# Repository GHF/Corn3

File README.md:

Corn3
=====
Copyright (C) 2014 Xo Wang

Corn3 is firmware for Corntroller version 3. It is a total rewrite of previous
Corntroller code, with a focus on writing code and documentation that may serve
as an introduction to three phase motor control for hobbyists.

Build
-----
Corn3 is written for use with GNU Tools for ARM Embedded Processors
(https://launchpad.net/gcc-arm-embedded).

To build, run make:

```
make
```

If you don't have arm-none-eabi in your PATH, specify its prefix in TRGT, e.g.:

```
make TRGT=~/gcc-arm-none-eabi-4_8-2014q3/bin/arm-none-eabi-
```

Hardware
--------
Corntroller is a small and efficient brushless motor controller.

Version 3.2 features:

  - 0.8 in by 1.6 in
  - STM32F3 microcontroller (ARM Cortex-M4 @ 72MHz)
  - TI DRV8301 gate driver, current sense amplifier, and buck converter
  - Three-phase inverter with SO8 N-FETs
  - Dual shunt current sense
  - Hall sensor inputs
  - Up to 30 V input voltage

No power figures available, but should be similar to hobby controllers of
similar size.

Hacking
-------
Corn3 and Corntroller are developed using the Black Magic Probe debugger.

See http://www.blacksphere.co.nz/main/blackmagic

Corntroller v3 has a 10-pin "mini" keyed JTAG header and a PicoBlade 4-pin
serial debug connector. The firmware does not yet support USB firmware
flashing.

License
-------
Corn3 is licensed under the MIT license with non-advertisement clause.

In compliance with the Apache license that ChibiOS configuration and low level
drivers are licensed under, the Apache License version 2.0 is included.

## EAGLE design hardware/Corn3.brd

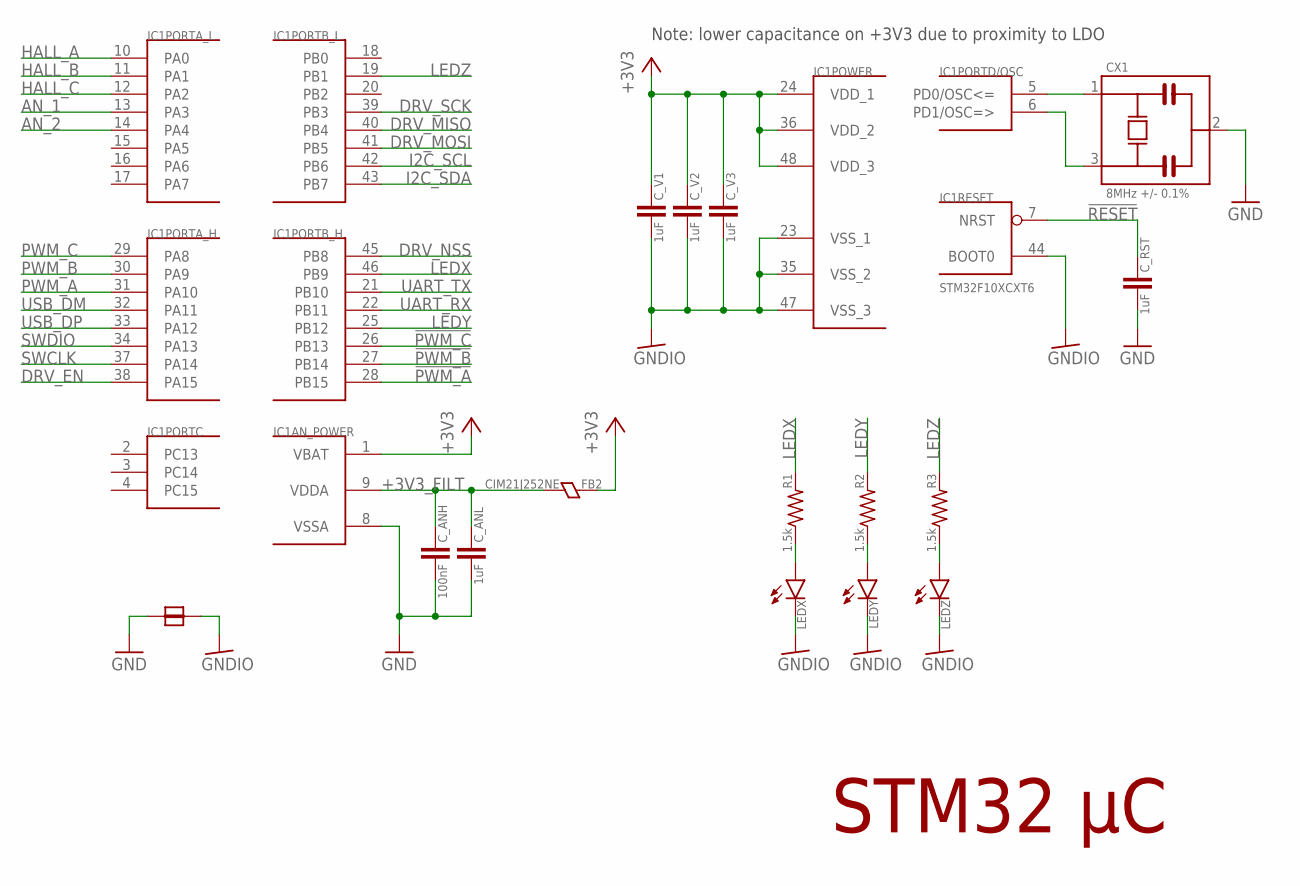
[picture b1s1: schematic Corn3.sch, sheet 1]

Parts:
CX1: 8MHz +/- 0.1%; MURATA_CSTCE
C_ANH: 100nF; 0603
C_ANL: 1uF; 0603
C_RST: 1uF; 0603
C_V1, C_V2, C_V3: 1uF; 0603
FB2: CIM21J252NE; 0805
IC1: STM32F10XCXT6; TQFP48
JUMPER-GND-GNDIO: JUMPER5025; 5025
LEDX: LED0805; 0805_POL
LEDY: LED0805; 0805_POL
LEDZ: LED0805; 0805_POL
R1, R2, R3: 1.5k; 0603

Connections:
!PWM_A: IC1.28 (PB15); also elsewhere on the board
!PWM_B: IC1.27 (PB14); also elsewhere on the board
!PWM_C: IC1.26 (PB13); also elsewhere on the board
!RESET: C_RST.1, IC1.7 (NRST); also elsewhere on the board
+3V3: C_V1.1, C_V2.1, C_V3.1, FB2.2, IC1.1 (VBAT), IC1.24 (VDD_1), IC1.36 (VDD_2), IC1.48 (VDD_3); also elsewhere on the board
+3V3_FILT: C_ANH.1, C_ANL.1, FB2.1, IC1.9 (VDDA); also elsewhere on the board
AN_1: IC1.13 (PA3); also elsewhere on the board
AN_2: IC1.14 (PA4); also elsewhere on the board
DRV_EN: IC1.38 (PA15); also elsewhere on the board
DRV_MISO: IC1.40 (PB4); also elsewhere on the board
DRV_MOSI: IC1.41 (PB5); also elsewhere on the board
DRV_NSS: IC1.45 (PB8); also elsewhere on the board
DRV_SCK: IC1.39 (PB3); also elsewhere on the board
GND: CX1.2, C_ANH.2, C_ANL.2, C_RST.2, IC1.8 (VSSA), JUMPER-GND-GNDIO.1; also elsewhere on the board
GNDIO: C_V1.2, C_V2.2, C_V3.2, IC1.23 (VSS_1), IC1.35 (VSS_2), IC1.44 (BOOT0), IC1.47 (VSS_3), JUMPER-GND-GNDIO.2, LEDX.- (C), LEDY.- (C), LEDZ.- (C)
HALL_A: IC1.10 (PA0); also elsewhere on the board
HALL_B: IC1.11 (PA1); also elsewhere on the board
HALL_C: IC1.12 (PA2); also elsewhere on the board
I2C_SCL: IC1.42 (PB6); also elsewhere on the board
I2C_SDA: IC1.43 (PB7); also elsewhere on the board
LEDX: IC1.46 (PB9), R1.2
LEDY: IC1.25 (PB12), R2.2
LEDZ: IC1.19 (PB1), R3.2
unnamed: CX1.3, IC1.6 (PD1/OSC=>)
unnamed: CX1.1, IC1.5 (PD0/OSC<=)
unnamed: LEDX.+ (A), R1.1
unnamed: LEDZ.+ (A), R3.1
unnamed: LEDY.+ (A), R2.1
PWM_A: IC1.31 (PA10); also elsewhere on the board
PWM_B: IC1.30 (PA9); also elsewhere on the board
PWM_C: IC1.29 (PA8); also elsewhere on the board
SWCLK: IC1.37 (PA14); also elsewhere on the board
SWDIO: IC1.34 (PA13); also elsewhere on the board
UART_RX: IC1.22 (PB11); also elsewhere on the board
UART_TX: IC1.21 (PB10); also elsewhere on the board
USB_DM: IC1.32 (PA11); also elsewhere on the board
USB_DP: IC1.33 (PA12); also elsewhere on the board

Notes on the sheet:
STM32 µC
Note: lower capacitance on +3V3 due to proximity to LDO

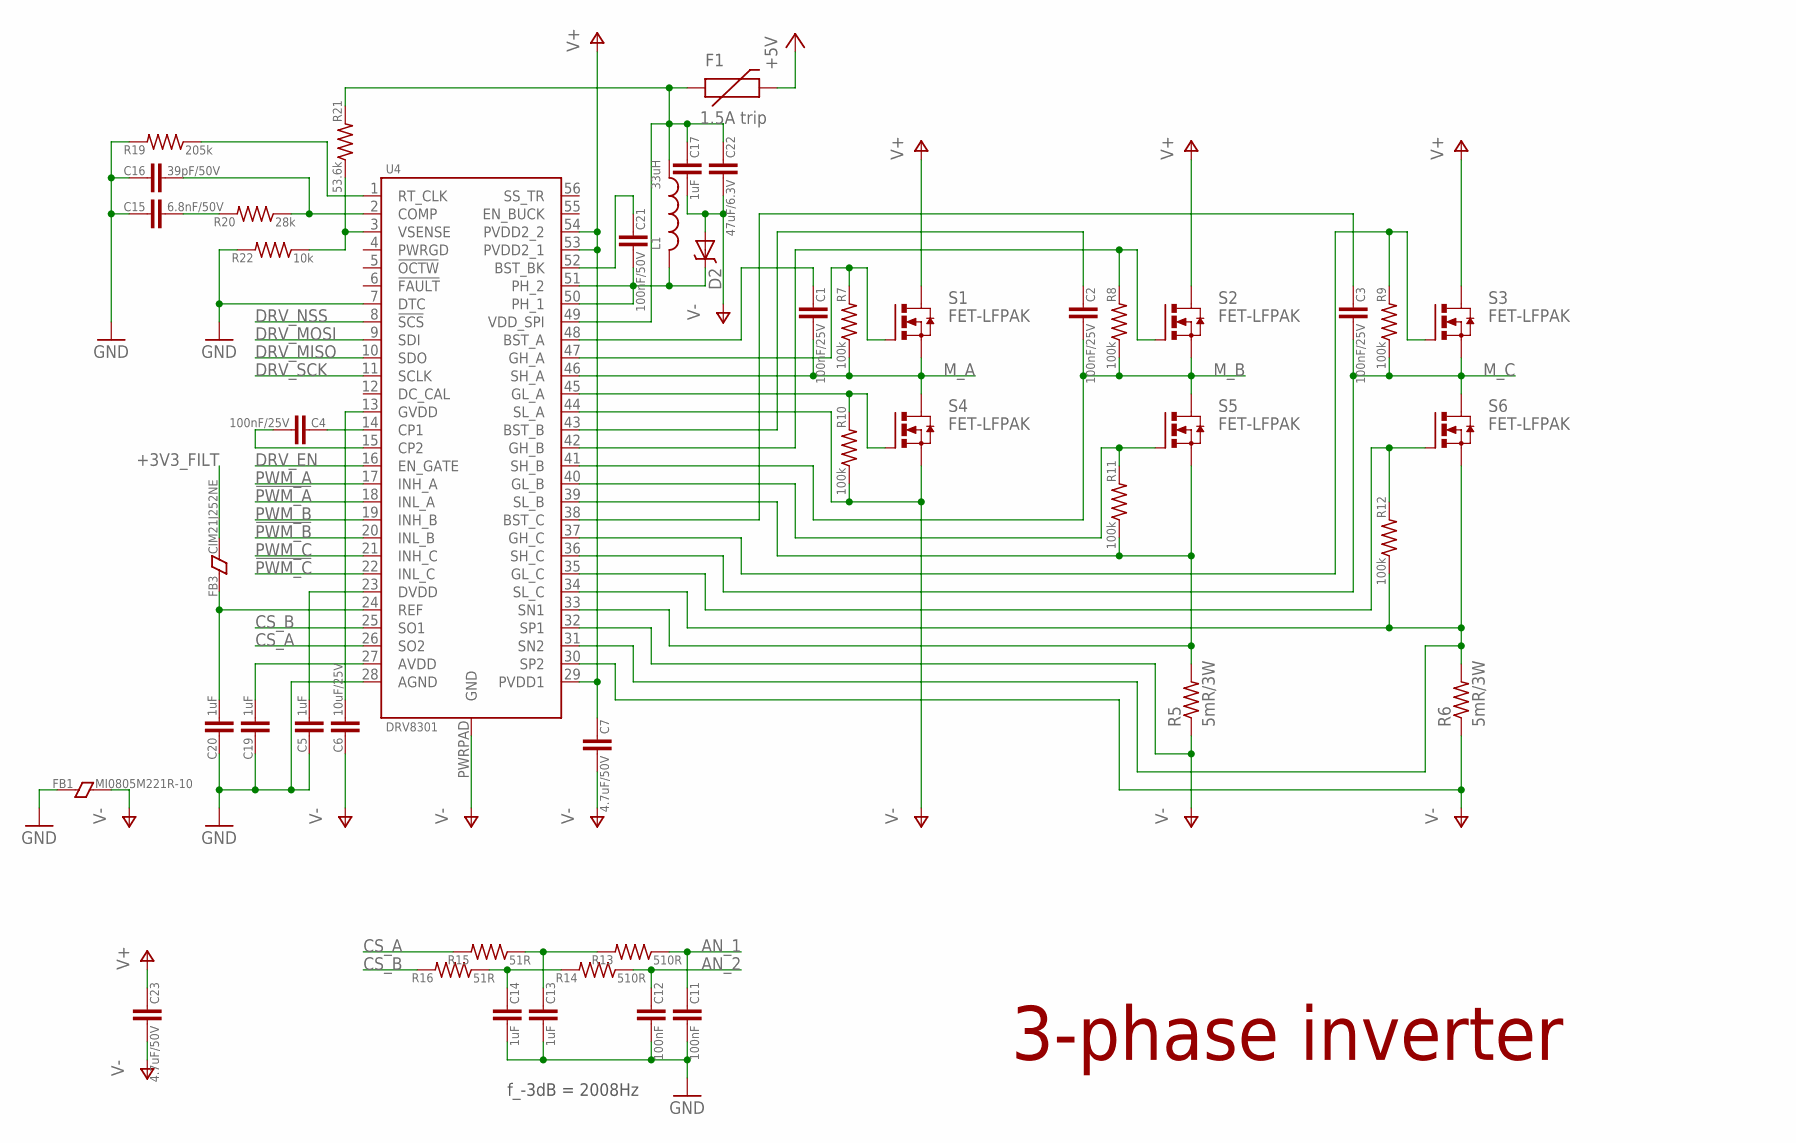
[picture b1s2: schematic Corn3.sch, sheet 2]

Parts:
C1, C2, C3, C4: 100nF/25V; 0603
C5, C13, C14, C17, C19, C20: 1uF; 0603
C6: 10uF/25V; 0805
C7, C23: 4.7uF/50V; 1206
C11, C12: 100nF; 0603
C15: 6.8nF/50V; 0603
C16: 39pF/50V; 0603
C21: 100nF/50V; 0603
C22: 47uF/6.3V; 0805
D2: DIODE-SCHOTTKY_; SMA-DIODE
F1: 1.5A trip; PTC-1206
FB1: MI0805M221R-10; 0805
FB3: CIM21J252NE; 0805
L1: 33uH; TAIYO-YUDEN_NR40
R5, R6: 5mR/3W; R2512
R7, R8, R9, R10, R11, R12: 100k; 0603
R13, R14: 510R; 0603
R15, R16: 51R; 0603
R19: 205k; 0603
R20: 28k; 0603
R21: 53.6k; 0603
R22: 10k; 0603
S1, S2, S3, S4, S5, S6: FET-LFPAK; SON-5X6
U4: DRV8301; HTSSOP-56

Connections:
!PWM_A: U4.18 (INL_A); also elsewhere on the board
!PWM_B: U4.20 (INL_B); also elsewhere on the board
!PWM_C: U4.22 (INL_C); also elsewhere on the board
+3V3_FILT: FB3.1; also elsewhere on the board
+5V: F1.2; also elsewhere on the board
AN_1: C11.1, R13.1; also elsewhere on the board
AN_2: C12.1, R14.1; also elsewhere on the board
CS_A: R15.2, U4.26 (SO2)
CS_B: R16.2, U4.25 (SO1)
DRV_EN: U4.16 (EN_GATE); also elsewhere on the board
DRV_MISO: U4.10 (SDO); also elsewhere on the board
DRV_MOSI: U4.9 (SDI); also elsewhere on the board
DRV_NSS: U4.8 (!SCS); also elsewhere on the board
DRV_SCK: U4.11 (SCLK); also elsewhere on the board
GND: C5.1, C11.2, C12.2, C13.2, C14.2, C15.1, C16.1, C19.1, C20.1, FB1.2, R19.2, R22.2, U4.7 (DTC), U4.28 (AGND); also elsewhere on the board
M_A: C1.2, R7.1, S1.S1 (S), S1.S2 (S), S1.S3 (S), S4.D, S4.D_ (D), U4.46 (SH_A)
M_B: C2.2, R8.1, S2.S1 (S), S2.S2 (S), S2.S3 (S), S5.D, S5.D_ (D), U4.41 (SH_B)
M_C: C3.2, R9.1, S3.S1 (S), S3.S2 (S), S3.S3 (S), S6.D, S6.D_ (D), U4.36 (SH_C)
unnamed: R8.2, S2.G, U4.42 (GH_B)
unnamed: R7.2, S1.G, U4.47 (GH_A)
unnamed: R12.2, S6.G, U4.35 (GL_C)
unnamed: R11.2, S5.G, U4.40 (GL_B)
unnamed: R9.2, S3.G, U4.37 (GH_C)
unnamed: C21.1, U4.52 (BST_BK)
unnamed: C1.1, U4.48 (BST_A)
unnamed: C2.1, U4.43 (BST_B)
unnamed: C3.1, U4.38 (BST_C)
unnamed: R10.2, S4.G, U4.45 (GL_A)
unnamed: C17.1, C22.1, F1.1, L1.1, R21.2, U4.49 (VDD_SPI)
unnamed: C16.2, R20.1, U4.2 (COMP)
unnamed: C14.1, R14.2, R16.1
unnamed: C13.1, R13.2, R15.1
unnamed: C15.2, R20.2
unnamed: R21.1, R22.1, U4.3 (VSENSE)
unnamed: C5.2, U4.23 (DVDD)
unnamed: C6.2, U4.13 (GVDD)
unnamed: C4.1, U4.14 (CP1)
unnamed: C4.2, U4.15 (CP2)
unnamed: C21.2, D2.C, L1.2, U4.50 (PH_1), U4.51 (PH_2)
unnamed: C20.2, FB3.2, U4.24 (REF)
unnamed: C19.2, U4.27 (AVDD)
unnamed: R19.1, U4.1 (RT_CLK)
PWM_A: U4.17 (INH_A); also elsewhere on the board
PWM_B: U4.19 (INH_B); also elsewhere on the board
PWM_C: U4.21 (INH_C); also elsewhere on the board
SL_B: R5.2, R11.1, S5.S1 (S), S5.S2 (S), S5.S3 (S), U4.33 (SN1), U4.39 (SL_B)
SL_C: R6.2, R12.1, S6.S1 (S), S6.S2 (S), S6.S3 (S), U4.31 (SN2), U4.34 (SL_C)
V+: C7.1, C23.1, S1.D, S1.D_ (D), S2.D, S2.D_ (D), S3.D, S3.D_ (D), U4.29 (PVDD1), U4.53 (PVDD2_1), U4.54 (PVDD2_2)
V-: C6.1, C7.2, C17.2, C22.2, C23.2, D2.A, FB1.1, R5.1, R6.1, R10.1, S4.S1 (S), S4.S2 (S), S4.S3 (S), U4.30 (SP2), U4.32 (SP1), U4.44 (SL_A), U4.PWRPAD (GND)

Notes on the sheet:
3-phase inverter
f_-3dB = 2008Hz

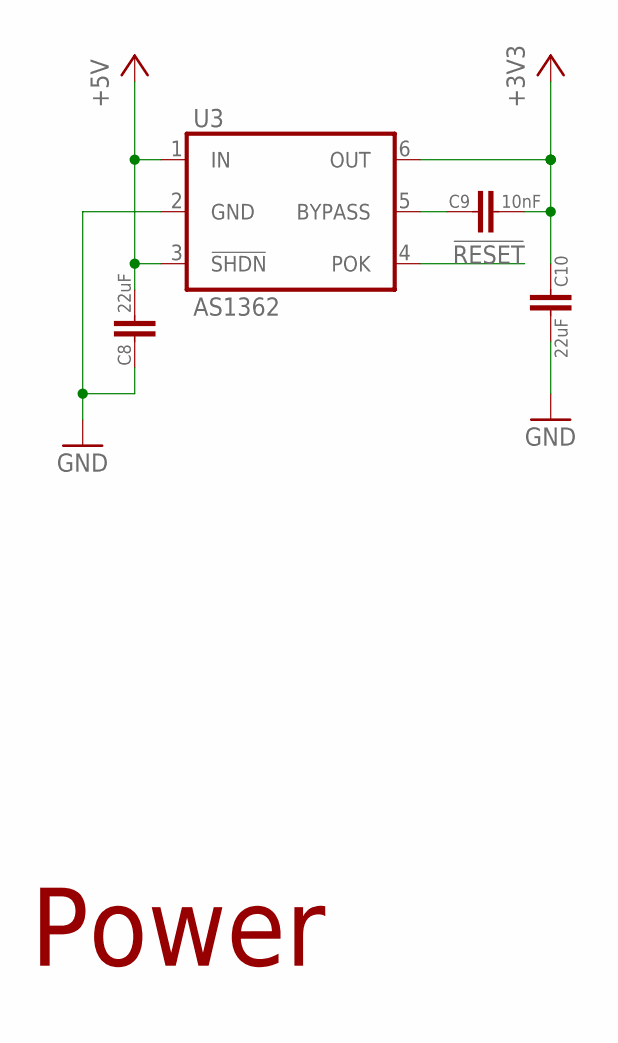
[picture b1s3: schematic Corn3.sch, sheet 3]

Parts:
C8, C10: 22uF; 0805
C9: 10nF; 0603
U3: AS1362; SOT23-6

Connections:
!RESET: U3.4 (POK); also elsewhere on the board
+3V3: C9.2, C10.1, U3.6 (OUT); also elsewhere on the board
+5V: C8.2, U3.1 (IN), U3.3 (!SHDN); also elsewhere on the board
GND: C8.1, C10.2, U3.2 (GND); also elsewhere on the board
unnamed: C9.1, U3.5 (BYPASS)

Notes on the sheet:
Power

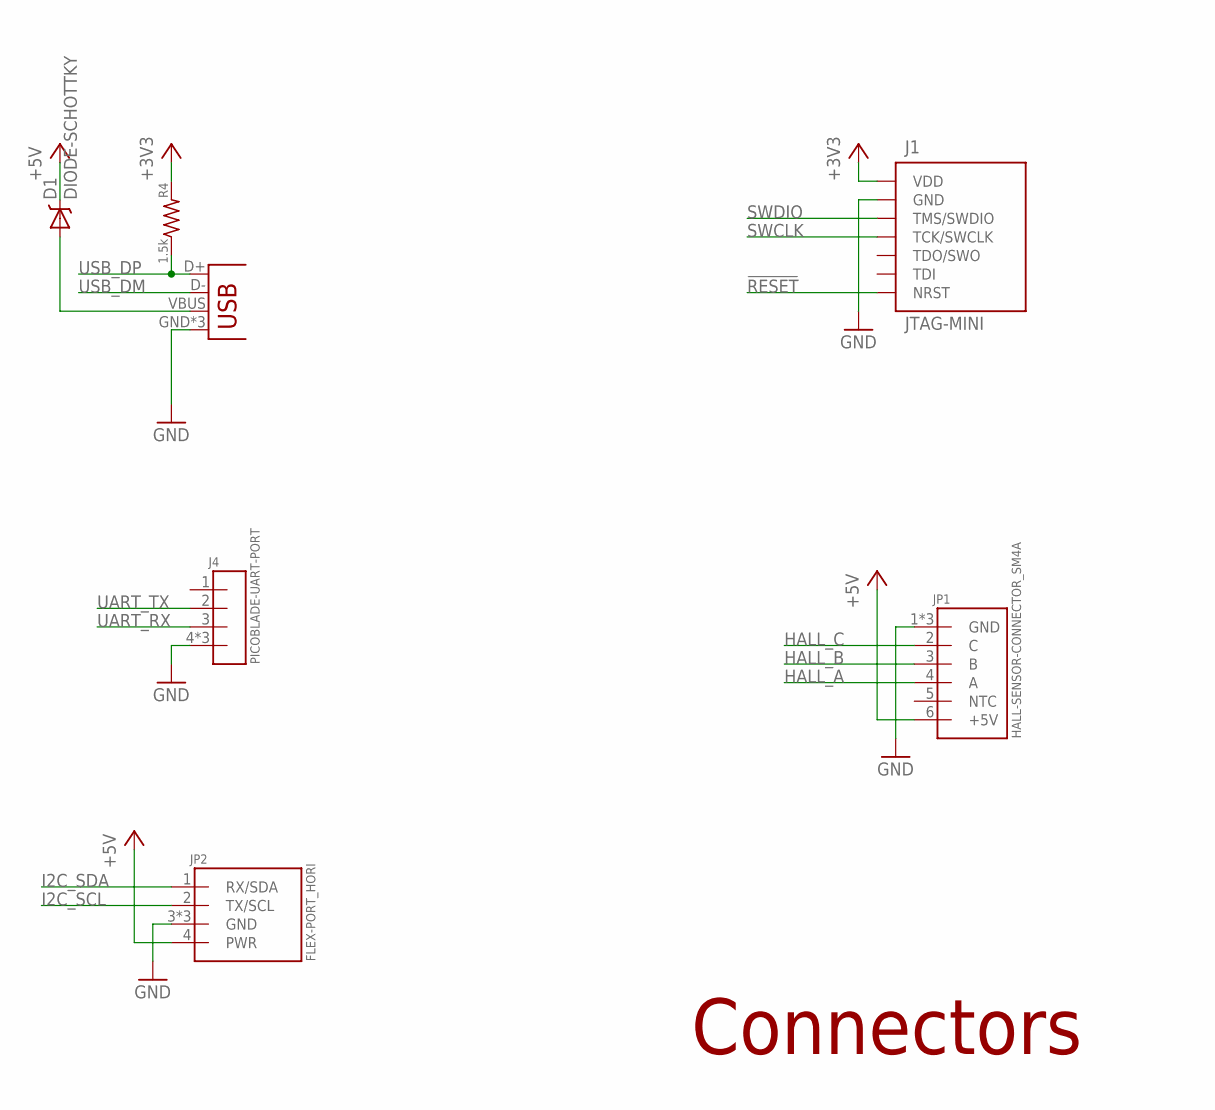
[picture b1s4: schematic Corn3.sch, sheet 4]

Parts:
D1: DIODE-SCHOTTKY; SOD-523
J1: JTAG-MINI
J4: PICOBLADE-UART-PORT; PICOBLADE-04-SMD-RA
JP1: HALL-SENSOR-CONNECTOR_SM4A; JST_S6B-ZR-SM4A
JP2: FLEX-PORT_HORI; JST_SM04B-SRSS
JP3: USB-MICROB
R4: 1.5k; 0603

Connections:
!RESET: J1.NRST; also elsewhere on the board
+3V3: J1.VDD, R4.2; also elsewhere on the board
+5V: D1.C, JP1.6 (+5V), JP2.4 (PWR); also elsewhere on the board
GND: J1.GND1 (GND), J1.GND2 (GND), J1.GND3 (GND), J1.GND4 (GND), J4.4, J4.TAB1 (4), J4.TAB2 (4), JP1.1 (GND), JP1.TAB1 (GND), JP1.TAB2 (GND), JP2.3 (GND), JP2.TAB1 (GND), JP2.TAB2 (GND), JP3.GND, JP3.MT1 (GND), JP3.MT2 (GND); also elsewhere on the board
HALL_A: JP1.4 (A); also elsewhere on the board
HALL_B: JP1.3 (B); also elsewhere on the board
HALL_C: JP1.2 (C); also elsewhere on the board
I2C_SCL: JP2.2 (TX/SCL); also elsewhere on the board
I2C_SDA: JP2.1 (RX/SDA); also elsewhere on the board
unnamed: D1.A, JP3.VBUS
SWCLK: J1.TCK (TCK/SWCLK); also elsewhere on the board
SWDIO: J1.TMS (TMS/SWDIO); also elsewhere on the board
UART_RX: J4.3; also elsewhere on the board
UART_TX: J4.2; also elsewhere on the board
USB_DM: JP3.D-; also elsewhere on the board
USB_DP: JP3.D+, R4.1; also elsewhere on the board

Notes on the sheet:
Connectors

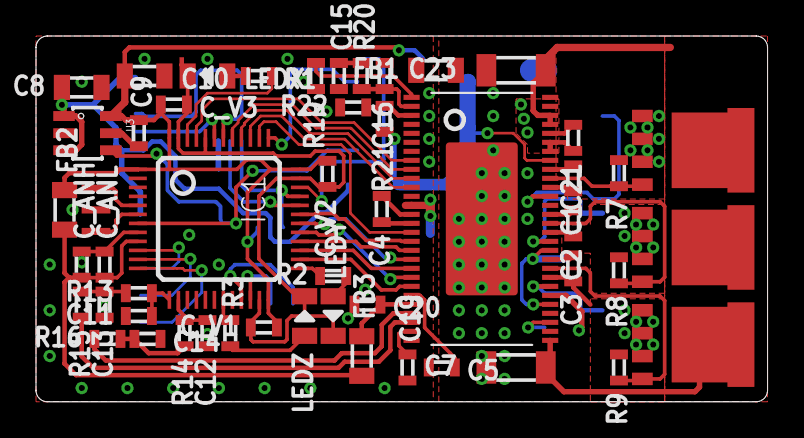
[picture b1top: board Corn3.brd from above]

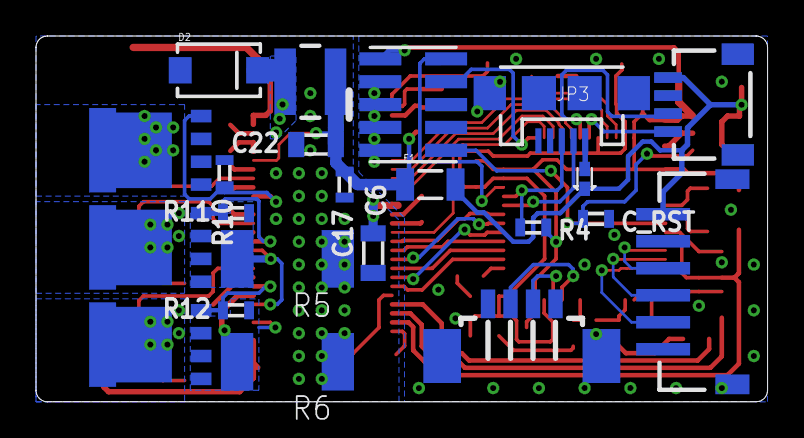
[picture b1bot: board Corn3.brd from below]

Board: 2 copper layers, 40.6 x 20.3 mm, 74 parts (22 on the bottom side), 73 nets.

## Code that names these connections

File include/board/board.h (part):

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/*
 * GPIOA setup:
 *
 * PA0  - HALL_A                    (alternate 1 pullup).
 * PA1  - HALL_B                    (alternate 1 pullup).
 * PA2  - HALL_C                    (alternate 1 pullup).
 * PA3  - PIN3                      (input pullup).
 * PA4  - PIN4                      (input pullup).
 * PA5  - PIN5                      (input pullup).
 * PA6  - PIN6                      (input pullup).
 * PA7  - PIN7                      (input pullup).
 * PA8  - PWM_C                     (alternate 6).
 * PA9  - PWM_B                     (alternate 6).
 * PA10 - PWM_A                     (alternate 6).
 * PA11 - USB_DM                    (alternate 14).
 * PA12 - USB_DP                    (alternate 14).
 * PA13 - SWDIO                     (alternate 0).
 * PA14 - SWCLK                     (alternate 0).
 * PA15 - DRV_EN                    (output).
 */
#define VAL_GPIOA_MODER             (PIN_MODE_ALTERNATE(GPIOA_HALL_A) |     \
                                     PIN_MODE_ALTERNATE(GPIOA_HALL_B) |     \
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 * GPIOB setup:
 *
 * PB0  - PIN0                      (input pullup).
 * PB1  - LEDZ                      (output).
 * PB2  - PIN2                      (input pullup).
 * PB3  - DRV_SCK                   (alternate 5).
 * PB4  - DRV_MISO                  (alternate 5).
 * PB5  - DRV_MOSI                  (alternate 5).
 * PB6  - PWM_IN                    (alternate 2).
 * PB7  - PIN7                      (input pullup).
 * PB8  - DRV_NSS                   (output).
 * PB9  - LEDX                      (output).
 * PB10 - UART_TX                   (alternate 7).
 * PB11 - UART_RX                   (alternate 7).
 * PB12 - LEDY                      (output).
 * PB13 - PWM_CN                    (alternate 6).
 * PB14 - PWM_BN                    (alternate 6).
 * PB15 - PWM_AN                    (alternate 4).
 */
#define VAL_GPIOB_MODER             (PIN_MODE_INPUT(GPIOB_PIN0) |           \
                                     PIN_MODE_OUTPUT(GPIOB_LEDZ) |          \
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/*
 * GPIOD setup:
 *
 * PD0  - PIN0                      (input pullup).
 * PD1  - PIN1                      (input pullup).
 * PD2  - PIN2                      (input pullup).
 * PD3  - PIN3                      (input pullup).
 * PD4  - PIN4                      (input pullup).
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
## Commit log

2014-01-19 Initial commit of configuration and build files.
    Functionality is blinking the heartbeat LED.
2014-01-20 Add hardware design files.
2014-01-20 Add UART capability.
2014-01-20 Add newlib-required syscalls to enable printf.
2014-01-20 Add .gdbinit to .gitignore.
2014-01-20 Add ANSI color codes to Utility.h.
2014-01-20 Add logging tools based on Python's logging library.
2014-01-20 Add mechanism for build timestamps and git version.
2014-01-20 Move board files to subdirectories in include and src.
2014-01-20 Make all log headings above DEBUG be bold.
2014-01-20 Move Utility and Logging to "base"; rename to lowercase names per style.
2014-01-21 Add input capture driver to "lld" subdir.
    Copied from ChibiOS's ICU low-level driver (lld) for STM32.
2014-01-21 Strip input capture support for timers other than TIM2.
2014-01-21 Add 32-bit timer support to input capture driver.
2014-01-21 Add inputs XOR option to input capture driver.
2014-01-22 Style variable names.
2014-01-22 Add initialization timer, tweak LEDs.
2014-01-22 Remove duplicate Config.h/config.h.
2014-01-22 Add stubs for C++ support without libstdc++.
2014-01-23 Make GetLoggingLevel static so it can be used in multiple compilation units.
2014-01-23 Add option to disable printf floating point support.
    Works by replacing newlib's double to string routine with a minimal stub.
2014-01-23 Allow base/logging to use chprintf instead of system printf.
2014-01-23 Refactor initialization code into its own files.
2014-01-23 Add __dso_handle and disable thread-safe static initialization.
    This allows static objects to be defined.
2014-01-23 Print function name when logging.
2014-01-26 Add reset options and channels 3 & 4 to ICU driver.
2014-01-27 Add workaround to ICU driver for timing issues.
    This makes the WAITING to ACTIVE transition generate a callback, and always clears the timer when enabling the ICU.
2014-01-27 Add color reset at beginning of welcome message.
2014-01-27 Add Hall-effect sensor rotor angle driver.
    This represents the beginnings of the motor module. Also enable ICU driver 2 in the OS, which this driver relies on.
2014-01-27 Fix include order per style.
2014-01-27 Add CHECK, an error-checking macro.
2014-01-30 Flip hall sensor bits.
2014-01-30 Fix backslashes in config per style.
2014-01-30 Disable UART flow control.
2014-01-30 Set error LED upon CriticalHalt.
2014-01-30 Fix CHECK macro arguments.
2014-02-02 Add DRV8303 configuration and error detection driver.
2014-02-02 Add new line to beginning of welcome message.
2014-02-02 Fix PWM pin modes to not create spurious inverter spikes on init.
2014-02-02 Add simple software filter for spurious hall edges.
    Also minor style change in constructor.
2014-02-02 Update ChibiOS and integrate changes to custom ICU low-level driver.
2014-02-03 Add PWM driver and inverter control interface.
    Driver has support for high impedance phases and deadtime insertion.
2014-02-03 Move PWM low level driver to lld dirs for customization.
2014-02-03 Make PWM generation center-aligned.
    Add cr1 field to PWM low level driver configuration.
2014-02-03 Add system reset functionality (two ^Cs over the debug serial).
    Add references to NVIC_SystemReset so it isn't optimized out and can be jumped to with the debugger.
    Minor changes per style.
2014-02-03 Update README.
2014-02-03 Separate driver initialization to separate Start functions.
    Rename DRV8303 methods to avoid confusion with "Start."
2014-02-04 Refacter Corn system into its own class.
2014-02-04 Fix channel B not being disabled bug.
2014-02-04 Reverse bits of hall sensor state to match hardware.
2014-02-04 Add six-step commutation (motor-driving) logic.
2014-02-04 Undo hall sensor bit reverse and fix look up tables instead.
    Change naming per style.
2014-02-05 Fix RotorHall not recognizing timer overflows.
2014-02-07 Add servo PWM input driver.
    Changes and fixes to input capture driver. Add integer math header to base. Edit board files for PWM input rather than I2C.
2014-02-07 Add full braking when throttle is zero.
2014-02-08 Disable motor drive when servo input capture times out.
2014-02-08 Poll gate driver for errors and reset as needed to clear errors.
2014-02-08 Add option to disable new/delete implementations.
    Saves code size by not linking malloc/free.
2014-02-08 Disable unused ChibiOS components.
2014-02-08 Disable debug options.
2014-08-04 Update ChibiOS and merge new Makefile options.
    Remove references to FW lib.
    Merge in fix to PWM LLD; merge ignored for ICU LLD because TIM9 isn't supported.
2014-09-06 Fix AS1362 silkscreen first pin mark (#3).
    Increase hardware rev to 3.1. Add labels for motor phases.
2014-09-06 Fix LED silkscreen polarity markings (#2).
2014-09-06 Add diode from USB V+ to +5V (#1).
2014-10-03 Add completed hardware v3.2 (#1, #4, #23, #24, #25).
2014-10-05 Fix minor nits with make rules.
2014-10-06 Update ChibiOS to latest (2.6.x and then some).
    Merge PWM and ICU changes to custom low-level drivers.
2014-10-19 Fix APB2 clock to run at the correct 72MHz.
2014-10-23 Update board config and README for hardware v3.2.
2014-10-23 Fix missing SZ/size utility in Makefile.
2014-10-23 Rename base/logging to base/log.
2014-10-23 Fix unintentional invocation of std::abs(double).
2014-10-23 Print project and version when starting build.
2014-10-24 Start hardware v3.3. Unserpentine SWCLK trace (#30).
2014-10-24 Fix reversed Hall connector (#31) and change pinout for flex port.
2014-10-24 Call NVIC_SystemReset through an attributed function.
    This is more robust and explicit than the function pointer indirection.
2014-10-25 Update to hardware v3.3.
    Slight changes to graphics (version, vanity, and copyright).
2014-10-26 Fix system calls.
    Rename syscalls.c to not conflict with ChibiOS provided source.
    All calls implement the reentrant variety.
    Make _sbrk (now _sbrk_r) is safe to call from ISRs.
    Remove unnecessary syscalls.
2014-10-27 Add USB support.
    Initialize USB CDC ACM device as an OS serial channel.
    Add device version macros and an ARRAY_SIZE utility macro.
2014-10-31 Minor style cleanup and USB docs.
2015-02-20 Add input capture hardware filtering support.
    Enabled with defaults for servo input and hall sensor input.
2015-02-24 Add servo input bounds checking.
    No pulse width beyond a margin past the servo input mapping endpoint is
    accepted as a valid servo input.
2015-02-24 Add Clamp function.
2015-02-24 Fix Average in base/integer.h for unsigned types.
2015-02-24 Reset timer counter at start of each servo pulse.
    Servo pulses are now zero-based so the capture register values are
    directly usable without overflow logic or rebasing against the previous
    falling edge capture.
2015-02-26 Add motor command slew rate limiting to servo input.

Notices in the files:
include/board/board.h:
ChibiOS/RT - Copyright (C) 2006-2013 Giovanni Di Sirio (MODIFIED BY ABOVE)
parts and their libraries:
SparkFun-Connectors: Licensing: CC v3.0 Share-Alike You are welcome to use this library for commercial purposes.
